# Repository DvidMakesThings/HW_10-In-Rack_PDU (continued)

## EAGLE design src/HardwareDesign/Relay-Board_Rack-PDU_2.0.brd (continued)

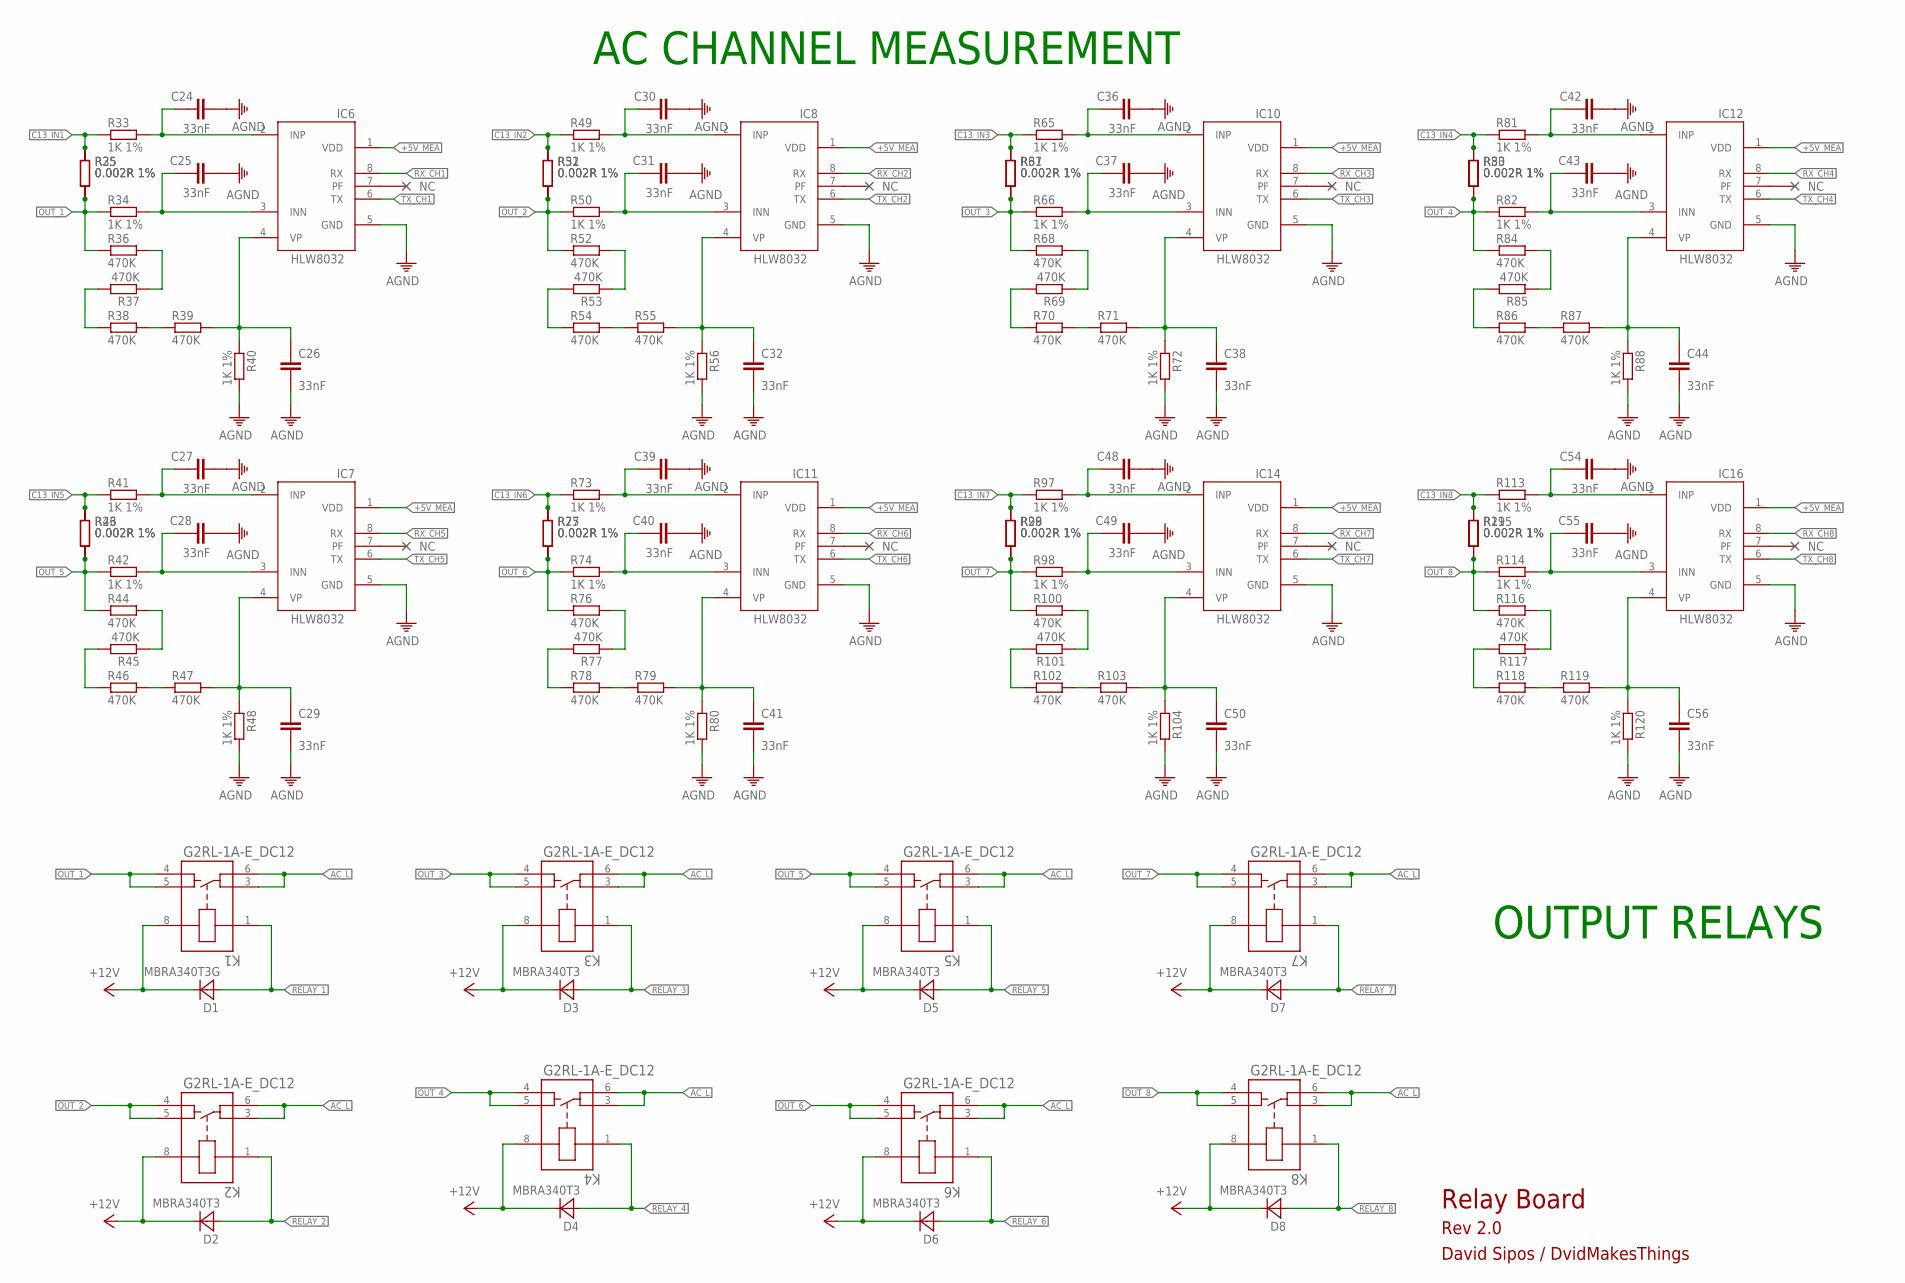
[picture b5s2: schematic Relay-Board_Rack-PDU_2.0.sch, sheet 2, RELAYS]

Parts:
C24, C25, C26, C27, C28, C29, C30, C31, C32, C36, C37, C38, C39, C40, C41, C42, C43, C44, C48, C49, C50, C54, C55, C56: 33nF; C1206
D1: MBRA340T3G; SMA
D2, D3, D4, D5, D6, D7, D8: MBRA340T3; SMA
IC6, IC7, IC8, IC10, IC11, IC12, IC14, IC16: HLW8032; SO8
K1, K2, K3, K4, K5, K6, K7, K8: G2RL-1A-E_DC12; RELAY_G2RL-1A-E_DC5_OMR
R25, R26, R27, R28, R29, R30, R31, R32, R35, R43, R51, R67, R75, R83, R99, R115: 0.002R 1%; 2512
R33, R34, R40, R41, R42, R48, R49, R50, R56, R65, R66, R72, R73, R74, R80, R81, R82, R88, R97, R98, R104, R113, R114, R120: 1K 1%; 1206
R36, R37, R38, R39, R44, R45, R46, R47, R52, R53, R54, R55, R68, R69, R70, R71, R76, R77, R78, R79, R84, R85, R86, R87, R100, R101, R102, R103, R116, R117, R118, R119: 470K; 1206

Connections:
+5V_MEA: IC6.1 (VDD), IC7.1 (VDD), IC8.1 (VDD), IC10.1 (VDD), IC11.1 (VDD), IC12.1 (VDD), IC14.1 (VDD), IC16.1 (VDD); also elsewhere on the board
+12V: D1.C, D2.C, D3.C, D4.C, D5.C, D6.C, D7.C, D8.C, K1.8, K2.8, K3.8, K4.8, K5.8, K6.8, K7.8, K8.8; also elsewhere on the board
AC_L: K1.3, K1.6, K2.3, K2.6, K3.3, K3.6, K4.3, K4.6, K5.3, K5.6, K6.3, K6.6, K7.3, K7.6, K8.3, K8.6; also elsewhere on the board
AGND: C24.2, C25.2, C26.2, C27.2, C28.2, C29.2, C30.2, C31.2, C32.2, C36.2, C37.2, C38.2, C39.2, C40.2, C41.2, C42.2, C43.2, C44.2, C48.2, C49.2, C50.2, C54.2, C55.2, C56.2, IC6.5 (GND), IC7.5 (GND), IC8.5 (GND), IC10.5 (GND), IC11.5 (GND), IC12.5 (GND), IC14.5 (GND), IC16.5 (GND), R40.2, R48.2, R56.2, R72.2, R80.2, R88.2, R104.2, R120.2; also elsewhere on the board
C13_IN1: R25.2, R33.1, R35.2
C13_IN2: R32.2, R49.1, R51.2
C13_IN3: R31.2, R65.1, R67.2
C13_IN4: R30.2, R81.1, R83.2
C13_IN5: R26.2, R41.1, R43.2
C13_IN6: R27.2, R73.1, R75.2
C13_IN7: R28.2, R97.1, R99.2
C13_IN8: R29.2, R113.1, R115.2
unnamed: C24.1, IC6.2 (INP), R33.2
unnamed: C25.1, IC6.3 (INN), R34.2
unnamed: R36.2, R37.1
unnamed: R37.2, R38.1
unnamed: R38.2, R39.1
unnamed: C26.1, IC6.4 (VP), R39.2, R40.1
unnamed: C27.1, IC7.2 (INP), R41.2
unnamed: C28.1, IC7.3 (INN), R42.2
unnamed: R44.2, R45.1
unnamed: R45.2, R46.1
unnamed: R46.2, R47.1
unnamed: C29.1, IC7.4 (VP), R47.2, R48.1
unnamed: C30.1, IC8.2 (INP), R49.2
unnamed: C31.1, IC8.3 (INN), R50.2
unnamed: R52.2, R53.1
unnamed: R53.2, R54.1
unnamed: R54.2, R55.1
unnamed: C32.1, IC8.4 (VP), R55.2, R56.1
unnamed: C36.1, IC10.2 (INP), R65.2
unnamed: C37.1, IC10.3 (INN), R66.2
unnamed: R68.2, R69.1
unnamed: R69.2, R70.1
unnamed: R70.2, R71.1
unnamed: C38.1, IC10.4 (VP), R71.2, R72.1
unnamed: C39.1, IC11.2 (INP), R73.2
unnamed: C40.1, IC11.3 (INN), R74.2
unnamed: R76.2, R77.1
unnamed: R77.2, R78.1
unnamed: R78.2, R79.1
unnamed: C41.1, IC11.4 (VP), R79.2, R80.1
unnamed: C42.1, IC12.2 (INP), R81.2
unnamed: C43.1, IC12.3 (INN), R82.2
unnamed: R84.2, R85.1
unnamed: R85.2, R86.1
unnamed: R86.2, R87.1
unnamed: C44.1, IC12.4 (VP), R87.2, R88.1
unnamed: C48.1, IC14.2 (INP), R97.2
unnamed: C49.1, IC14.3 (INN), R98.2
unnamed: R100.2, R101.1
unnamed: R101.2, R102.1
unnamed: R102.2, R103.1
unnamed: C50.1, IC14.4 (VP), R103.2, R104.1
unnamed: C54.1, IC16.2 (INP), R113.2
unnamed: C55.1, IC16.3 (INN), R114.2
unnamed: R116.2, R117.1
unnamed: R117.2, R118.1
unnamed: R118.2, R119.1
unnamed: C56.1, IC16.4 (VP), R119.2, R120.1
OUT_1: K1.4, K1.5, R25.1, R34.1, R35.1, R36.1
OUT_2: K2.4, K2.5, R32.1, R50.1, R51.1, R52.1
OUT_3: K3.4, K3.5, R31.1, R66.1, R67.1, R68.1
OUT_4: K4.4, K4.5, R30.1, R82.1, R83.1, R84.1
OUT_5: K5.4, K5.5, R26.1, R42.1, R43.1, R44.1
OUT_6: K6.4, K6.5, R27.1, R74.1, R75.1, R76.1
OUT_7: K7.4, K7.5, R28.1, R98.1, R99.1, R100.1
OUT_8: K8.4, K8.5, R29.1, R114.1, R115.1, R116.1
RELAY_1: D1.A, K1.1; also elsewhere on the board
RELAY_2: D2.A, K2.1; also elsewhere on the board
RELAY_3: D3.A, K3.1; also elsewhere on the board
RELAY_4: D4.A, K4.1; also elsewhere on the board
RELAY_5: D5.A, K5.1; also elsewhere on the board
RELAY_6: D6.A, K6.1; also elsewhere on the board
RELAY_7: D7.A, K7.1; also elsewhere on the board
RELAY_8: D8.A, K8.1; also elsewhere on the board
RX_CH1: IC6.8 (RX)
RX_CH2: IC8.8 (RX)
RX_CH3: IC10.8 (RX)
RX_CH4: IC12.8 (RX)
RX_CH5: IC7.8 (RX)
RX_CH6: IC11.8 (RX)
RX_CH7: IC14.8 (RX)
RX_CH8: IC16.8 (RX)
TX_CH1: IC6.6 (TX); also elsewhere on the board
TX_CH2: IC8.6 (TX); also elsewhere on the board
TX_CH3: IC10.6 (TX); also elsewhere on the board
TX_CH4: IC12.6 (TX); also elsewhere on the board
TX_CH5: IC7.6 (TX); also elsewhere on the board
TX_CH6: IC11.6 (TX); also elsewhere on the board
TX_CH7: IC14.6 (TX); also elsewhere on the board
TX_CH8: IC16.6 (TX); also elsewhere on the board

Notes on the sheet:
OUTPUT RELAYS
Relay Board
Rev 2.0
David Sipos / DvidMakesThings
AC CHANNEL MEASUREMENT

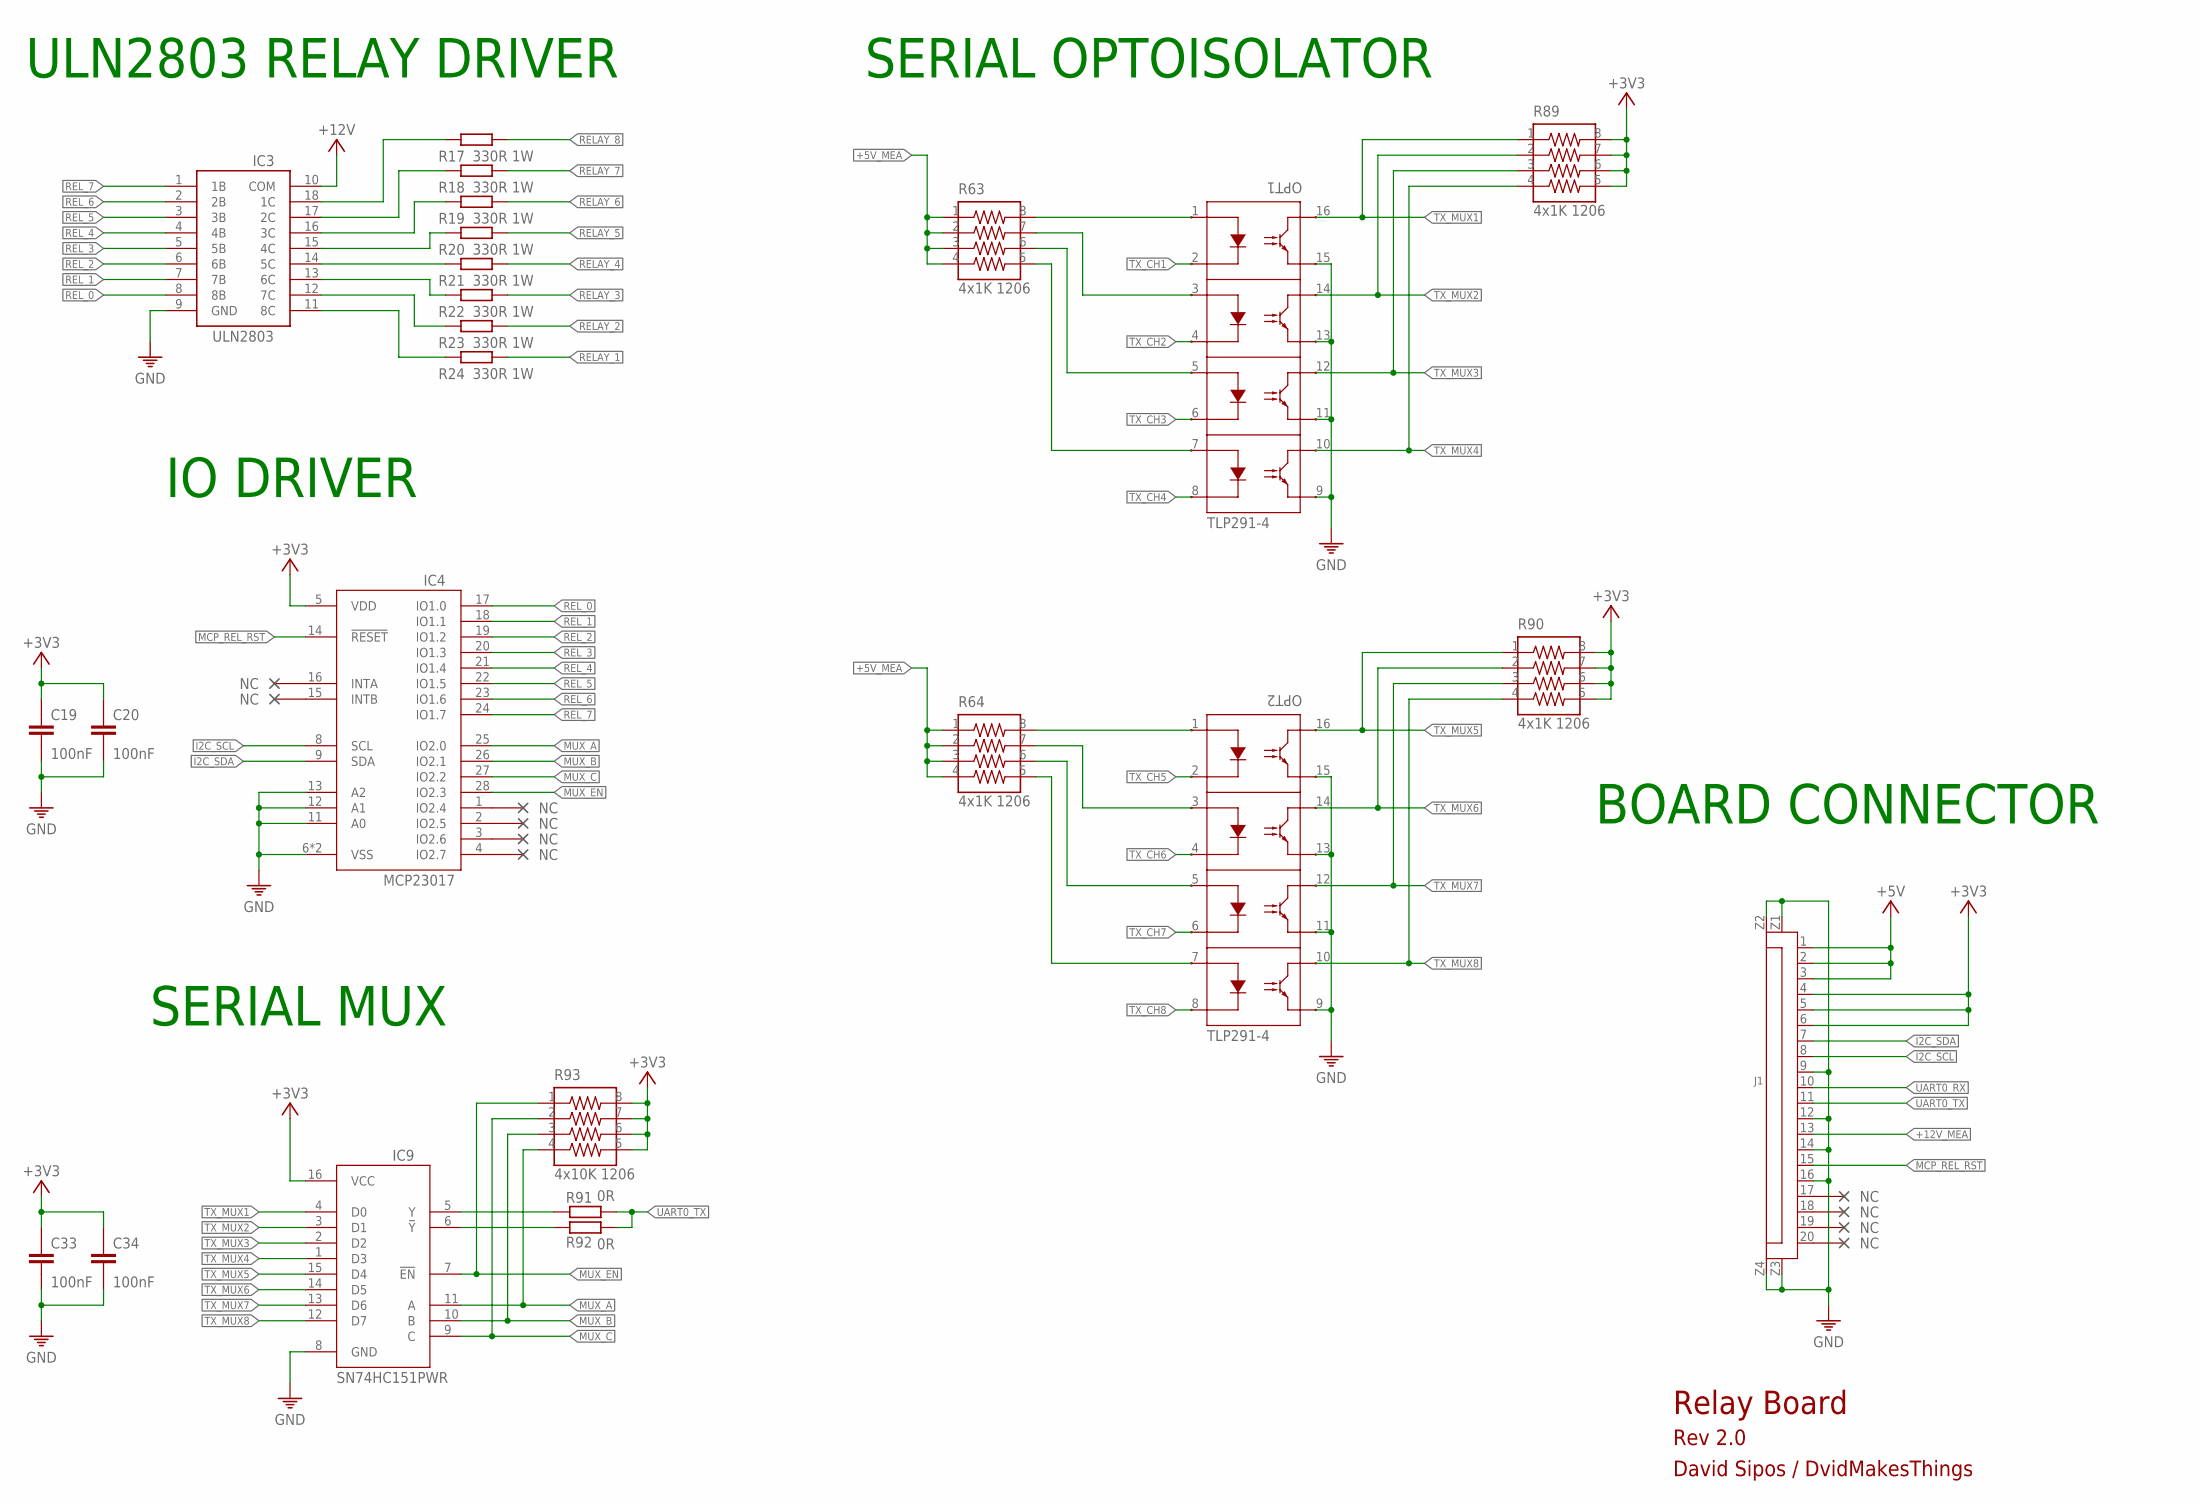
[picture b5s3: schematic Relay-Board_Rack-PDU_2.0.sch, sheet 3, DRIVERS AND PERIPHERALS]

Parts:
C19, C20, C33, C34: 100nF; C0402
IC3: ULN2803A; SO18
IC4: MCP23017-E/ML; QFN28[6X6]ML
IC9: SN74HC151PWR; TSSOP16
J1: FPC20-H; FPC20
OPT1, OPT2: TLP291-4; SO16
R17, R18, R19, R20, R21, R22, R23, R24: 330R 1W; 1206
R63, R64, R89, R90: 4x1K 1206; 742C083103JP
R91, R92: 0R; 0402
R93: 4x10K 1206; 742C083103JP

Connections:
+3V3: C19.1, C20.1, C33.1, C34.1, IC4.5 (VDD), IC9.16 (VCC), J1.4, J1.5, J1.6, R89.5, R89.6, R89.7, R89.8, R90.5, R90.6, R90.7, R90.8, R93.5, R93.6, R93.7, R93.8; also elsewhere on the board
+5V: J1.1, J1.2, J1.3; also elsewhere on the board
+5V_MEA: R63.1, R63.2, R63.3, R63.4, R64.1, R64.2, R64.3, R64.4; also elsewhere on the board
+12V: IC3.10 (COM); also elsewhere on the board
+12V_MEA: J1.13; also elsewhere on the board
GND: C19.2, C20.2, C33.2, C34.2, IC3.9 (GND), IC4.6 (VSS), IC4.11 (A0), IC4.12 (A1), IC4.13 (A2), IC4.PAD (VSS), IC9.8 (GND), J1.9, J1.12, J1.14, J1.16, J1.Z1, J1.Z2, J1.Z3, J1.Z4, OPT1.9, OPT1.11, OPT1.13, OPT1.15, OPT2.9, OPT2.11, OPT2.13, OPT2.15; also elsewhere on the board
I2C_SCL: IC4.8 (SCL), J1.8
I2C_SDA: IC4.9 (SDA), J1.7
MCP_REL_RST: IC4.14 (!RESET), J1.15
MUX_A: IC4.25 (IO2.0), IC9.11 (A), R93.4
MUX_B: IC4.26 (IO2.1), IC9.10 (B), R93.3
MUX_C: IC4.27 (IO2.2), IC9.9 (C), R93.2
MUX_EN: IC4.28 (IO2.3), IC9.7 (!EN), R93.1
unnamed: IC9.5 (Y), R91.1
unnamed: IC3.14 (5C), R21.1
unnamed: OPT1.1, R63.8
unnamed: IC3.11 (8C), R24.1
unnamed: IC3.12 (7C), R23.1
unnamed: IC3.13 (6C), R22.1
unnamed: OPT1.3, R63.7
unnamed: IC3.15 (4C), R20.1
unnamed: IC3.16 (3C), R19.1
unnamed: IC3.17 (2C), R18.1
unnamed: IC3.18 (1C), R17.1
unnamed: OPT1.5, R63.6
unnamed: OPT1.7, R63.5
unnamed: IC9.6 (!Y), R92.1
unnamed: OPT2.1, R64.8
unnamed: OPT2.3, R64.7
unnamed: OPT2.5, R64.6
unnamed: OPT2.7, R64.5
RELAY_1: R24.2; also elsewhere on the board
RELAY_2: R23.2; also elsewhere on the board
RELAY_3: R22.2; also elsewhere on the board
RELAY_4: R21.2; also elsewhere on the board
RELAY_5: R20.2; also elsewhere on the board
RELAY_6: R19.2; also elsewhere on the board
RELAY_7: R18.2; also elsewhere on the board
RELAY_8: R17.2; also elsewhere on the board
REL_0: IC3.8 (8B), IC4.17 (IO1.0)
REL_1: IC3.7 (7B), IC4.18 (IO1.1)
REL_2: IC3.6 (6B), IC4.19 (IO1.2)
REL_3: IC3.5 (5B), IC4.20 (IO1.3)
REL_4: IC3.4 (4B), IC4.21 (IO1.4)
REL_5: IC3.3 (3B), IC4.22 (IO1.5)
REL_6: IC3.2 (2B), IC4.23 (IO1.6)
REL_7: IC3.1 (1B), IC4.24 (IO1.7)
TX_CH1: OPT1.2; also elsewhere on the board
TX_CH2: OPT1.4; also elsewhere on the board
TX_CH3: OPT1.6; also elsewhere on the board
TX_CH4: OPT1.8; also elsewhere on the board
TX_CH5: OPT2.2; also elsewhere on the board
TX_CH6: OPT2.4; also elsewhere on the board
TX_CH7: OPT2.6; also elsewhere on the board
TX_CH8: OPT2.8; also elsewhere on the board
TX_MUX1: IC9.4 (D0), OPT1.16, R89.1
TX_MUX2: IC9.3 (D1), OPT1.14, R89.2
TX_MUX3: IC9.2 (D2), OPT1.12, R89.3
TX_MUX4: IC9.1 (D3), OPT1.10, R89.4
TX_MUX5: IC9.15 (D4), OPT2.16, R90.1
TX_MUX6: IC9.14 (D5), OPT2.14, R90.2
TX_MUX7: IC9.13 (D6), OPT2.12, R90.3
TX_MUX8: IC9.12 (D7), OPT2.10, R90.4
UART0_RX: J1.10
UART0_TX: J1.11, R91.2, R92.2

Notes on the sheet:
Relay Board
Rev 2.0
David Sipos / DvidMakesThings
ULN2803 RELAY DRIVER
IO DRIVER
SERIAL MUX
SERIAL OPTOISOLATOR
BOARD CONNECTOR

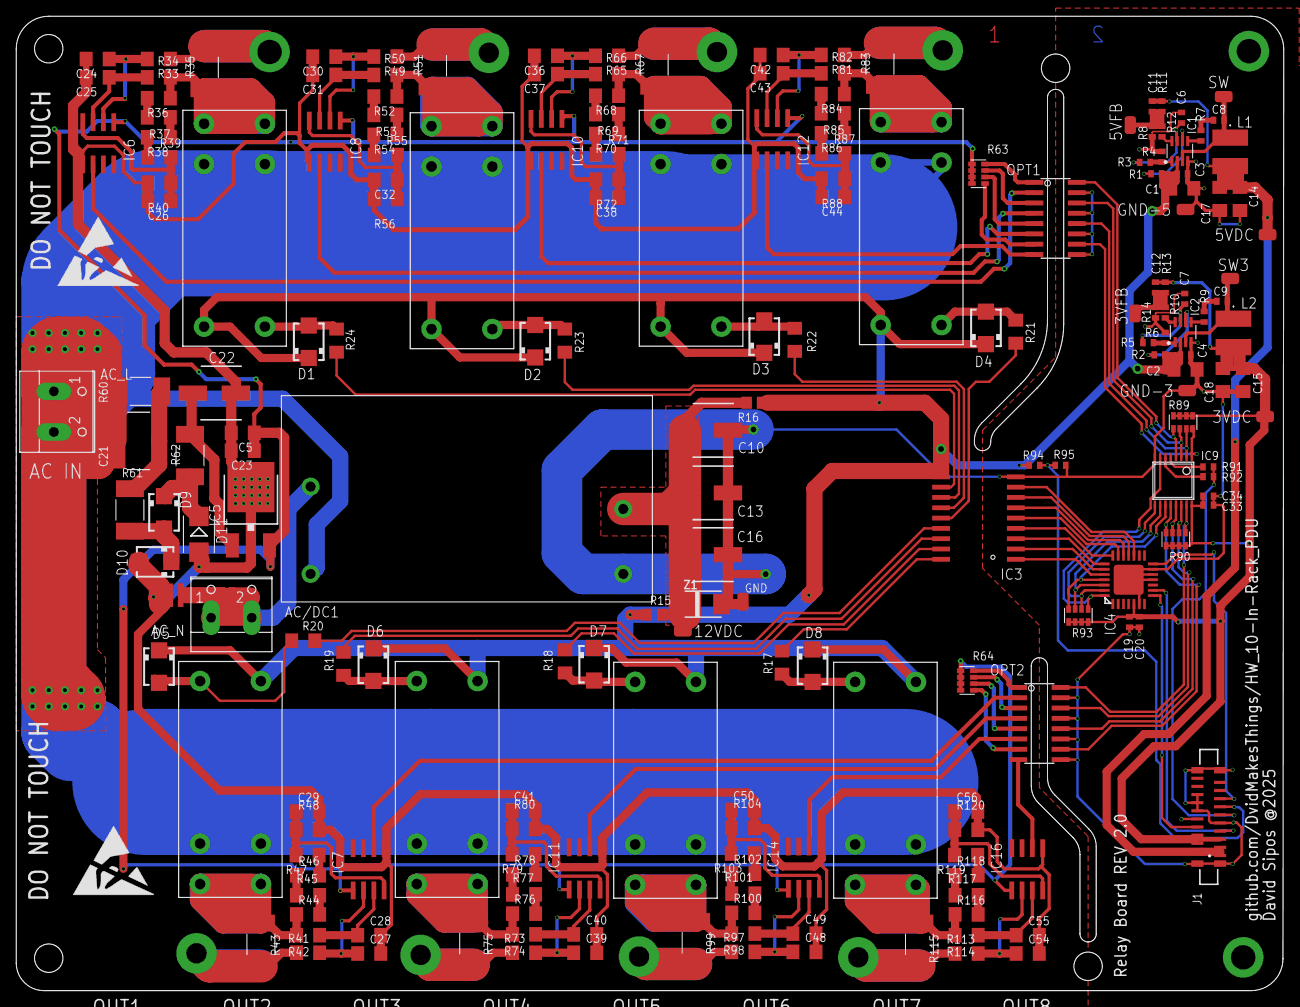
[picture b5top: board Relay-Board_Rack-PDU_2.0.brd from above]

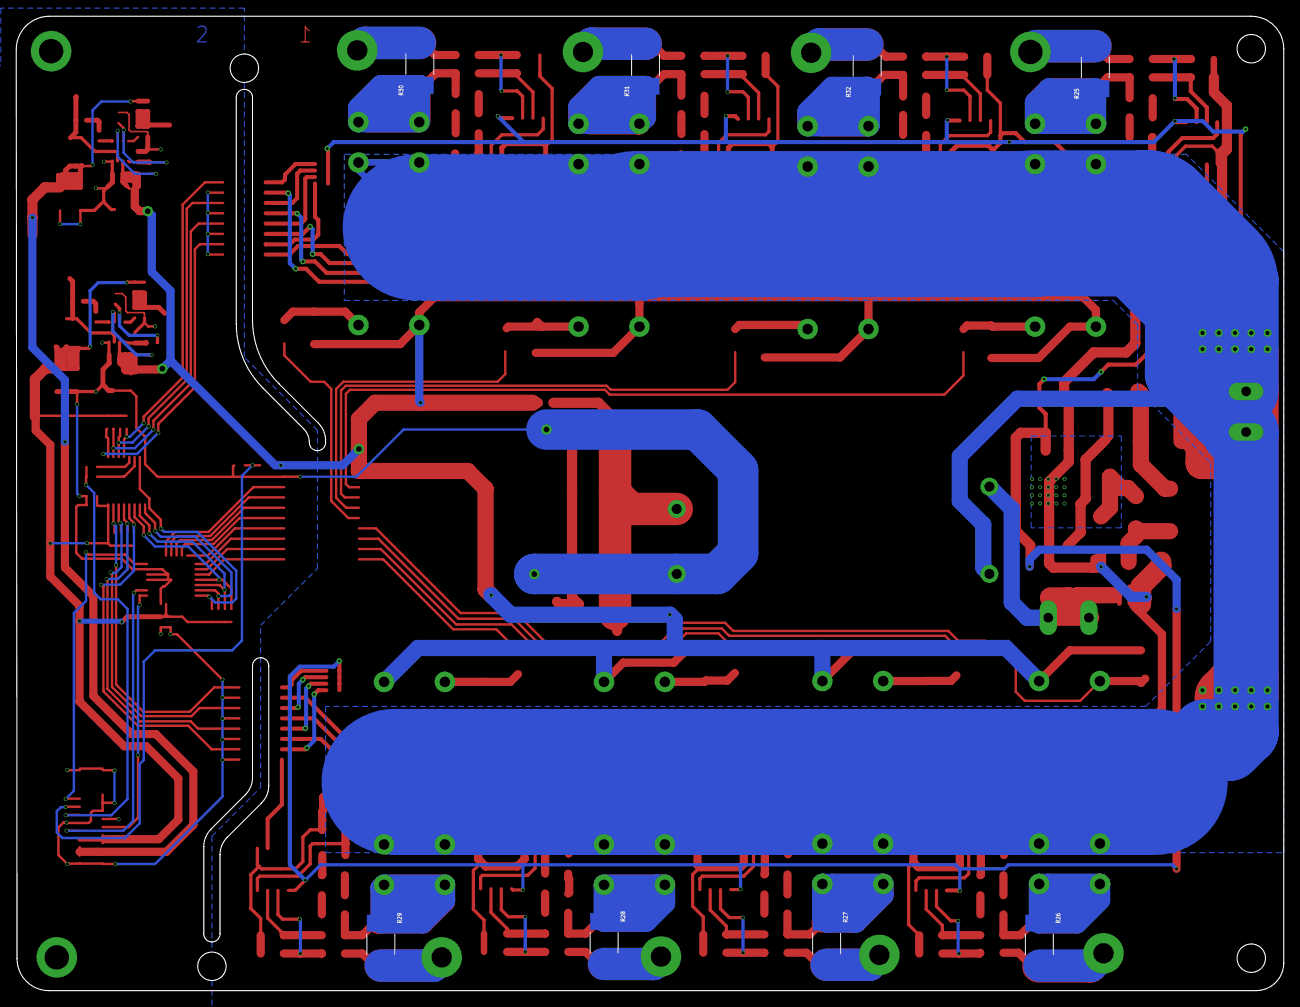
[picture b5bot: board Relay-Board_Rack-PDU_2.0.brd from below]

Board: 2 copper layers, 156.1 x 120.0 mm, 215 parts (8 on the bottom side), 152 nets.

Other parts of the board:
U$1, U$2: ESD_10.00
U$3: 2-LAYER
